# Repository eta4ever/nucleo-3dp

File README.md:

3D printer shield and heater boards for Nucleo-F411RE

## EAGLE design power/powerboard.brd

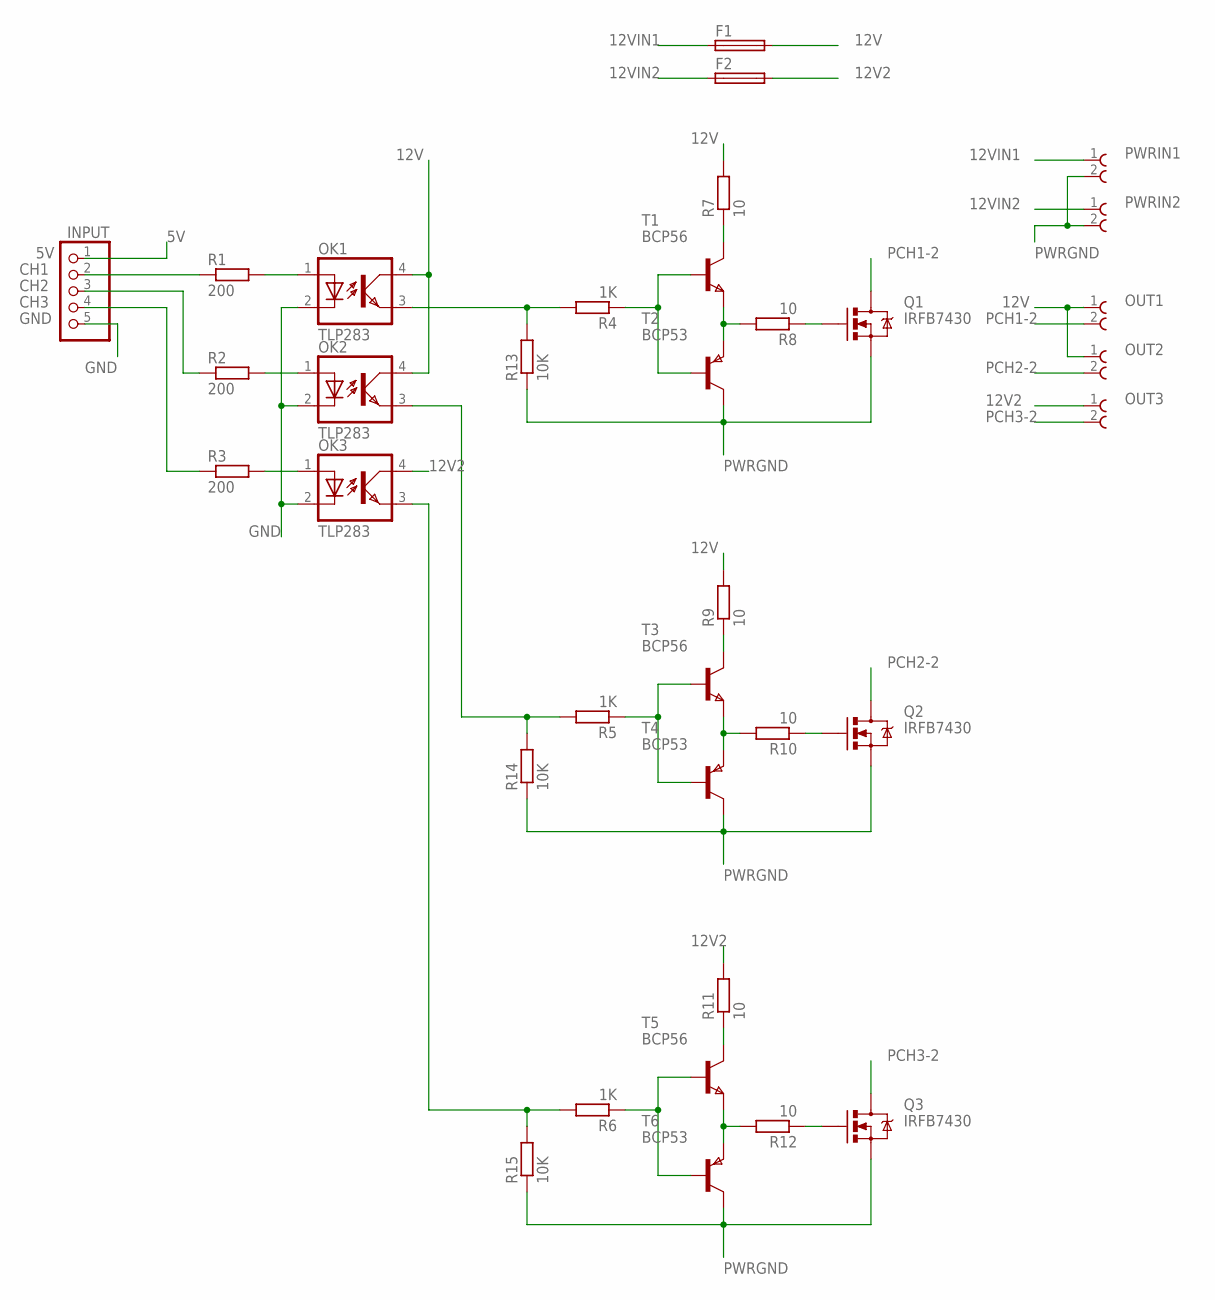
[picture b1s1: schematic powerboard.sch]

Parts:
F1, F2: SH22,5
INPUT: PINHD-1X5; 1X05
OK1, OK2, OK3: TLP283; MINI-FLAT-4
OUT1, OUT2, OUT3: 691244610002
PWRIN1, PWRIN2: 691244610002
Q1, Q2, Q3: IRFB7430; TO220V
R1, R2, R3: 200; R0805
R4, R5, R6: 1K; R0805
R7, R8, R9, R10, R11, R12: 10; R0805
R13, R14, R15: 10K; R0805
T1, T3, T5: BCP56; SOT223
T2, T4, T6: BCP53; SOT223

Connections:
5V: INPUT.1
12V: F1.2, OK1.4 (COL), OK2.4 (COL), OUT1.1, OUT2.1, R7.2, R9.2
12V2: F2.2, OK3.4 (COL), OUT3.1, R11.2
12VIN1: F1.1, PWRIN1.1
12VIN2: F2.1, PWRIN2.1
CH1: INPUT.2, R1.1
CH2: INPUT.3, R2.1
CH3: INPUT.4, R3.1
GND: INPUT.5, OK1.2 (C), OK2.2 (C), OK3.2 (C)
unnamed: OK1.1 (A), R1.2
unnamed: OK2.1 (A), R2.2
unnamed: R8.2, T1.3 (E), T2.3 (E)
unnamed: OK3.1 (A), R3.2
unnamed: R4.1, T1.1 (B), T2.1 (B)
unnamed: R5.1, T3.1 (B), T4.1 (B)
unnamed: OK1.3 (EMIT), R4.2, R13.2
unnamed: R7.1, T1.2 (C), T1.4 (C)
unnamed: Q1.1 (G), R8.1
unnamed: R10.2, T3.3 (E), T4.3 (E)
unnamed: OK3.3 (EMIT), R6.2, R15.2
unnamed: R9.1, T3.2 (C), T3.4 (C)
unnamed: Q2.1 (G), R10.1
unnamed: R12.2, T5.3 (E), T6.3 (E)
unnamed: R6.1, T5.1 (B), T6.1 (B)
unnamed: R11.1, T5.2 (C), T5.4 (C)
unnamed: Q3.1 (G), R12.1
unnamed: OK2.3 (EMIT), R5.2, R14.2
PCH1-2: OUT1.2, Q1.2 (D)
PCH2-2: OUT2.2, Q2.2 (D)
PCH3-2: OUT3.2, Q3.2 (D)
PWRGND: PWRIN1.2, PWRIN2.2, Q1.3 (S), Q2.3 (S), Q3.3 (S), R13.1, R14.1, R15.1, T2.2 (C), T2.4 (C), T4.2 (C), T4.4 (C), T6.2 (C), T6.4 (C)

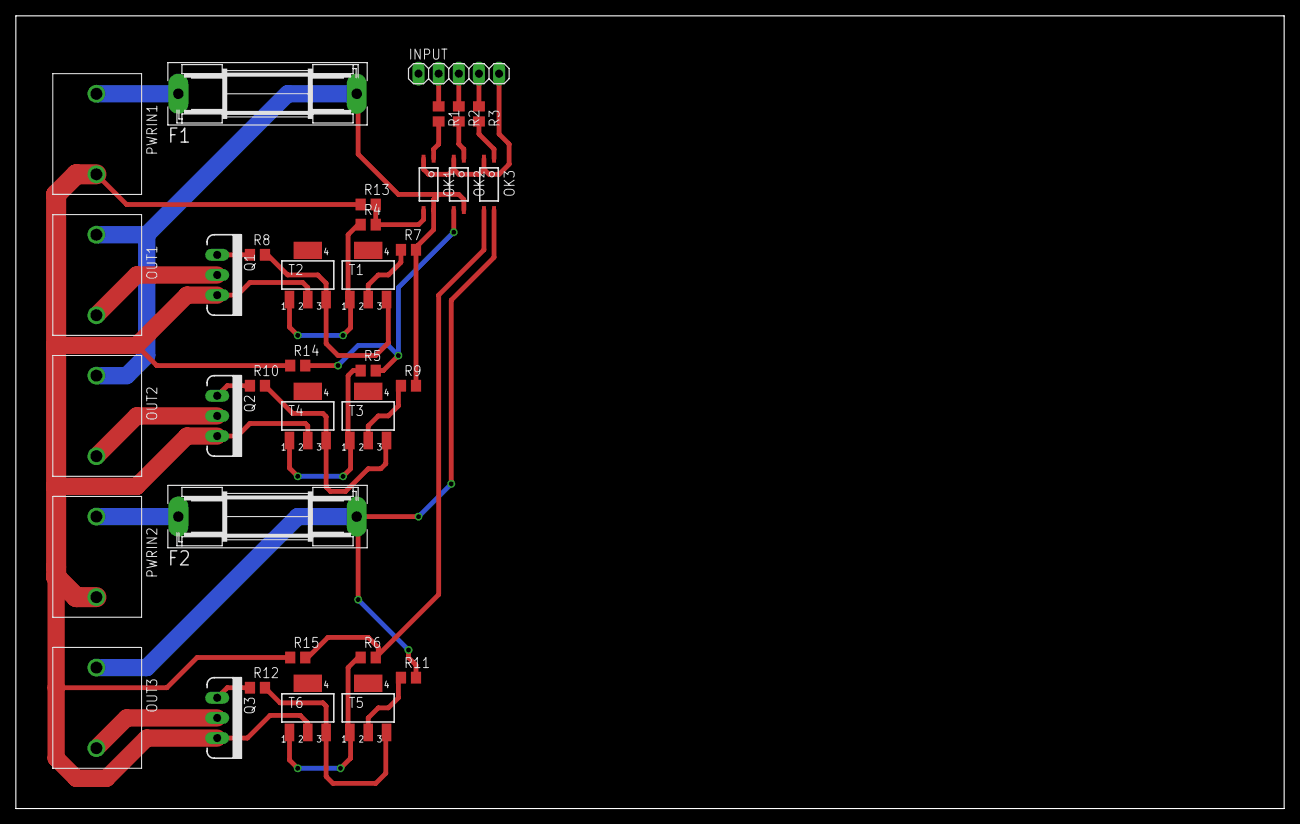
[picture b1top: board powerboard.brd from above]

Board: 2 copper layers, 160.0 x 100.0 mm, 35 parts (0 on the bottom side), 30 nets.

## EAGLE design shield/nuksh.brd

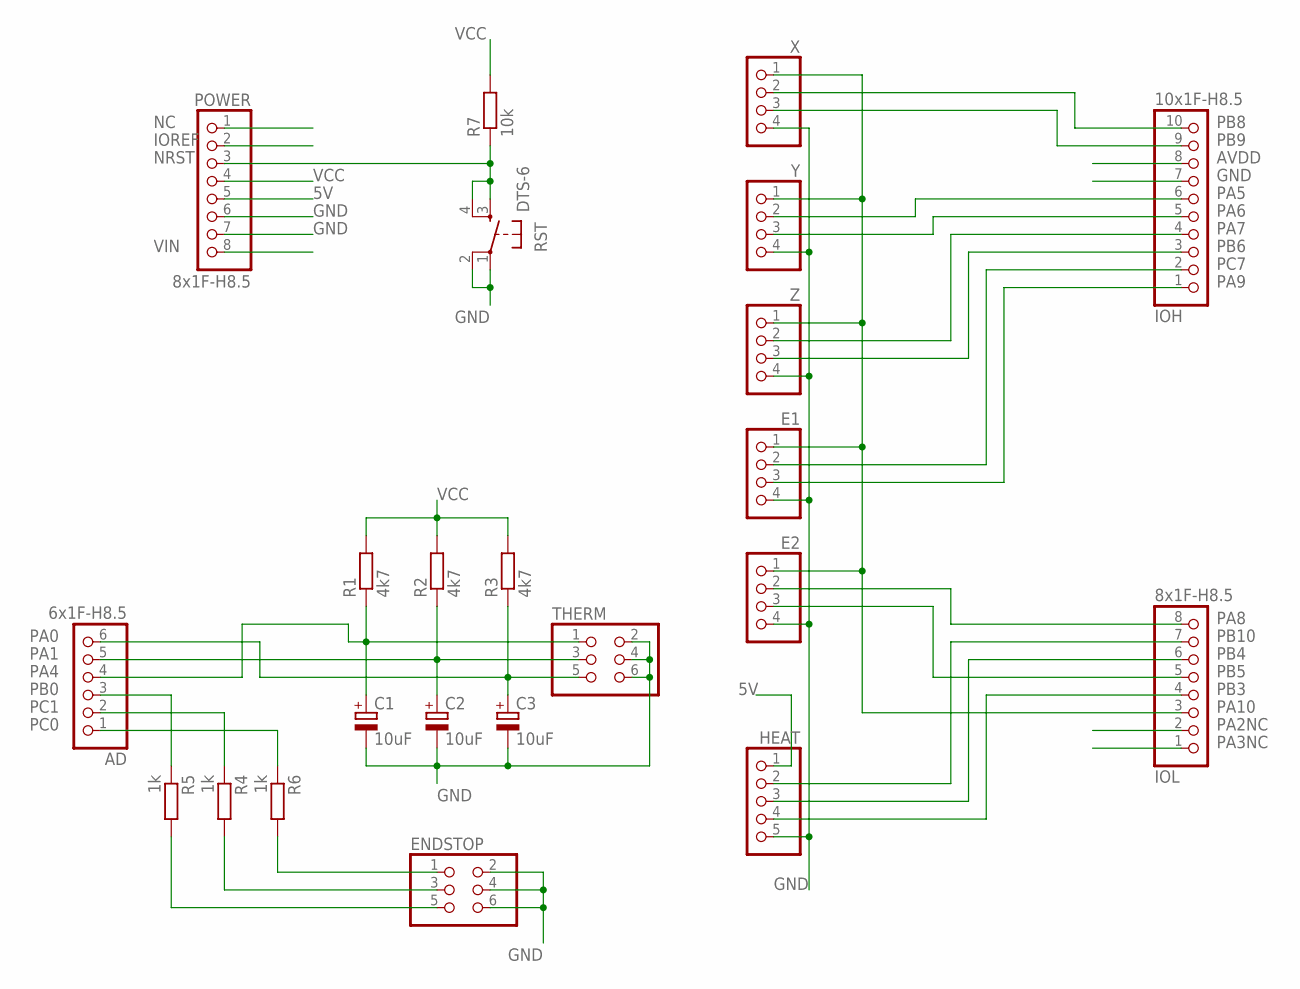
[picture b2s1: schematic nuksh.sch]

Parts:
AD: 6x1F-H8.5; 1X06
C1, C2, C3: 10uF; 153CLV-0605
E1, E2: PINHD-1X4; 1X04
ENDSTOP: PINHD-2X3; 2X03
HEAT: PINHD-1X5; 1X05
IOH: 10x1F-H8.5; 1X10
IOL: 8x1F-H8.5; 1X08
POWER: 8x1F-H8.5; 1X08
R1, R2, R3: 4k7; R0805
R4, R5, R6: 1k; R0805
R7: 10k; R0805
RST: DTS-6
THERM: PINHD-2X3; 2X03
X: PINHD-1X4; 1X04
Y: PINHD-1X4; 1X04
Z: PINHD-1X4; 1X04

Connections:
5V: HEAT.1, POWER.5
AVDD: IOH.8
GND: C1.-, C2.-, C3.-, E1.4, E2.4, ENDSTOP.2, ENDSTOP.4, ENDSTOP.6, HEAT.5, IOH.7, POWER.6, POWER.7, RST.1, RST.2, THERM.2, THERM.4, THERM.6, X.4, Y.4, Z.4
IOREF: POWER.2
unnamed: ENDSTOP.5, R5.2
unnamed: ENDSTOP.3, R4.2
unnamed: ENDSTOP.1, R6.2
NC: POWER.1
NRST: POWER.3, R7.1, RST.3, RST.4
PA0: AD.4, C1.+, R1.1, THERM.1
PA1: AD.5, C2.+, R2.1, THERM.3
PA2NC: IOL.2
PA3NC: IOL.1
PA4: AD.6, C3.+, R3.1, THERM.5
PA5: IOH.6, Y.2
PA6: IOH.5, Y.3
PA7: IOH.4, Z.2
PA8: E2.2, IOL.8
PA9: E1.3, IOH.1
PA10: E1.1, E2.1, IOL.3, X.1, Y.1, Z.1
PB0: AD.3, R5.1
PB3: HEAT.4, IOL.4
PB4: HEAT.3, IOL.6
PB5: E2.3, IOL.5
PB6: IOH.3, Z.3
PB8: IOH.10, X.2
PB9: IOH.9, X.3
PB10: HEAT.2, IOL.7
PC0: AD.1, R6.1
PC1: AD.2, R4.1
PC7: E1.2, IOH.2
VCC: POWER.4, R1.2, R2.2, R3.2, R7.2
VIN: POWER.8

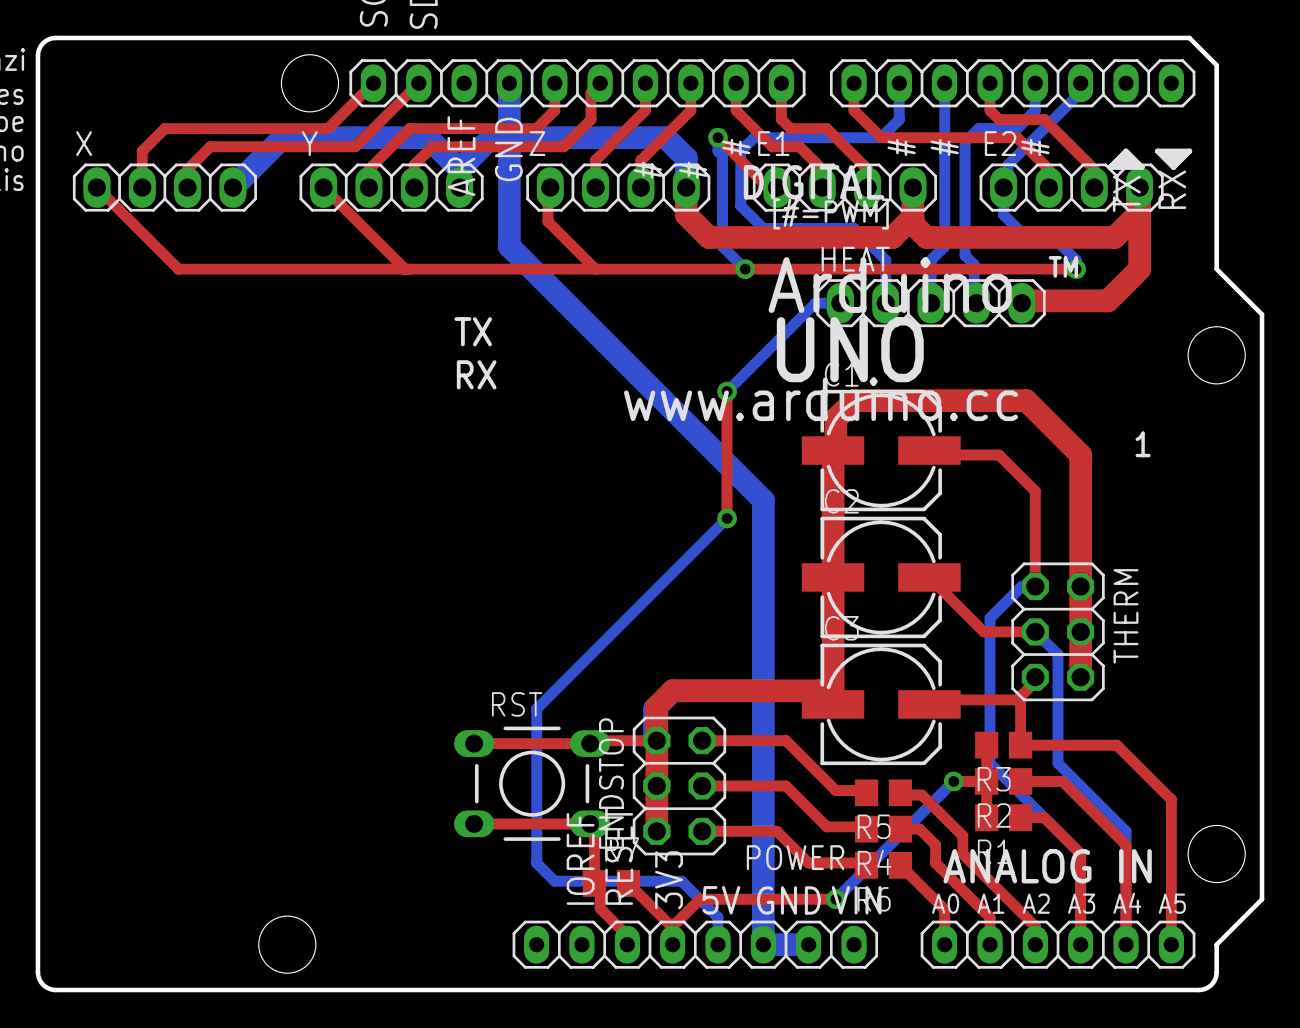
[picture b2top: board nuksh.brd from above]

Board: 2 copper layers, 68.6 x 53.3 mm, 23 parts (0 on the bottom side), 27 nets.

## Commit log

2017-02-27 :octocat: Added .gitattributes
2017-02-27 initial
2017-02-27 license
2017-02-27 power brd

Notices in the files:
parts and their libraries:
Terminal_Blocks_Connectors_rev15e: Copyright: Würth Elektronik
SparkFun-DiscreteSemi: Licensing: CC v3.0 Share-Alike You are welcome to use this library for commercial purposes.
